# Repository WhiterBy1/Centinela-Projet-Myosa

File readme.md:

# CENTINELA — Arquitectura de Firmware y Procesamiento de Datos

**Versión:** borrador v0.1
**Base:** esquemático KiCad (ESP32-S2-WROVER + MPU6050 + BMP280 + APDS-9960 + OLED + buzzer + Adafruit Feather M0 RFM9x)

Este documento define, a nivel de código, cómo el firmware de la pulsera CENTINELA adquiere datos de cada sensor, cómo se procesan, qué valores finales produce y cómo esos valores se usan para decidir y transmitir una alerta.

---

## 1. Resumen del sistema

CENTINELA es una pulsera IoT/Edge AI que detecta inmovilidad anómala sostenida en trabajadores agrícolas aislados. El ESP32-S2 corre un clasificador TinyML sobre datos inerciales del MPU6050. Si detecta una posible caída/incapacitación, abre una ventana de confirmación de 60 s en la que el trabajador puede cancelar con un gesto (APDS-9960). Si no cancela, se transmite una alerta por LoRa a una estación base y se visualiza en una torre de control web.

### 1.1 Diagrama de flujo general

Vista de extremo a extremo: desde la muestra cruda del IMU hasta que la alerta aparece en la torre de control. Detalle de cada bloque en las secciones 4 a 7.

```mermaid
flowchart TD
    A["MPU6050: accel/gyro @ 50 Hz"] --> B["Filtro DLPF (hardware, ~20 Hz)"]
    B --> C["Ventana deslizante (64 muestras, 75% solape)"]
    C --> D["Extracción de features"]
    D --> E["Clasificador TinyML (int8)"]
    E --> F{"score >= 0.75?"}
    F -- No --> G["consecutive_immobile = 0"]
    G --> C
    F -- Si --> H["consecutive_immobile++"]
    H --> I{"consecutive_immobile >= 8 ventanas?"}
    I -- No --> C
    I -- Si --> J["EV_SUSPECTED_IMMOBILITY"]

    J --> K["STATE_SUSPECTED_IMMOBILITY\nOLED + buzzer patrón bajo"]
    K --> L["STATE_CONFIRMATION_WINDOW (60 s)"]
    L --> M{"Gesto de cancelación\n(APDS-9960)?"}
    M -- Si --> N["STATE_NORMAL\n+ log de falso positivo"]
    M -- "No (timeout 60s)" --> O["Armar centinela_packet_t"]

    P["BMP280: temperatura"] -.->|"severity_bonus"| O
    Q["APDS-9960: gesto de zona"] -.->|"zone_id"| O

    O --> R["STATE_ALERT_TRANSMITTING\n(envío por LoRa vía Feather M0)"]
    R --> S{"ACK recibido?"}
    S -- "No (timeout ACK)" --> T{"reintentos < N?"}
    T -- Si --> R
    T -- No --> U["Modo baliza persistente"]
    S -- Si --> V["STATE_ALERT_ACKED\nbuzzer confirmación + OLED"]
    V --> W["Estación base"]
    W --> X["Torre de control web\n(panel del supervisor)"]
```

---

## 2. Mapa de hardware y buses

Según el esquemático:

| Componente | Ref. | Interfaz | Notas |
|---|---|---|---|
| MPU6050 (IMU) | U1 | I2C compartido (SDAD/SCLD) | VLOGIC/VDD a 3.3V, AD0 a GND → dirección 0x68 |
| BMP280 (temp/presión) | U2 | I2C compartido (SDAD/SCLD) | Sustituye al BMP180 mencionado en la propuesta original |
| APDS-9960 (gestos/proximidad/luz) | U3 | I2C compartido (SDAD/SCLD) + línea INT dedicada | INT usado como interrupción de gesto/wake |
| OLED 0.91" | U5 | I2C compartido (SDAD/SCLD) | Solo display, sin touch |
| Buzzer | BZ1 | GPIO digital directo | Control por PWM/tono |
| Adafruit Feather M0 RFM9x (LoRa) | A1 | SPI (SCK/MOSI/MISO) + UART (RX/TX) + I2C + EN/RESET | Actúa como **co-procesador de radio**, no como módulo RFM9x desnudo |

**Nota importante sobre el bloque LoRa:** el esquemático conecta al Feather M0 casi todos sus buses (SPI, UART, I2C, EN/RESET). Esto implica una decisión de arquitectura que conviene fijar por escrito antes de programar:

- **Opción A — SPI directo:** el ESP32-S2 es maestro SPI y el Feather M0 corre un firmware "esclavo" que traduce comandos SPI a operaciones del RFM9x (RadioHead/LoRa.h). Más rápido, pero requiere firmware custom en el SAMD21 del Feather.
- **Opción B — UART tipo módem:** el Feather M0 corre un firmware con protocolo de comandos simple sobre RX/TX (similar a comandos AT), y el ESP32 solo envía/recibe tramas de texto o binarias por serial. Más simple de depurar, menor throughput.

Se recomienda **Opción B (UART)** para el prototipo por velocidad de desarrollo, dejando SPI como mejora futura si se necesita menor latencia. *(Pendiente de confirmar según lo que ya se implementó en el Feather.)*

Todos los sensores I2C comparten bus, por lo que el firmware debe direccionarlos individualmente (direcciones por defecto: MPU6050 `0x68`, BMP280 `0x76/0x77`, APDS-9960 `0x39`, OLED SSD1306-like `0x3C`).

---

## 3. Arquitectura de firmware (FreeRTOS, dual-core)

El ESP32-S2 corre FreeRTOS con tareas repartidas así:

```
Core 0 (protocol/sensor core)          Core 1 (application core)
├── Task_SensorAcquisition (50 Hz)     ├── Task_Inference (TinyML)
├── Task_EnvSample (1 Hz, BMP280)      ├── Task_StateMachine
├── Task_GestureISR (event-driven)     ├── Task_LoRaComm
└── Task_PowerMgmt                     └── Task_UI (OLED + buzzer)
```

Comunicación entre tareas vía colas (`QueueHandle_t`) y un buffer circular protegido por mutex para las muestras del IMU.

```c
// Buffer de ventana deslizante para el clasificador
#define WINDOW_SIZE   64      // muestras (a 50 Hz ≈ 1.28 s de ventana)
#define WINDOW_STRIDE 16      // solape del 75%

typedef struct {
  int16_t ax, ay, az;   // acelerómetro crudo (LSB)
  int16_t gx, gy, gz;   // giroscopio crudo (LSB)
  uint32_t t_ms;
} imu_sample_t;

static imu_sample_t imu_window[WINDOW_SIZE];
static SemaphoreHandle_t imu_mutex;
static QueueHandle_t q_inference_result;
static QueueHandle_t q_state_events;
```

---

## 4. Adquisición de datos por dispositivo

### 4.1 MPU6050 — sensor primario del clasificador

- **Datos crudos:** aceleración (ax, ay, az) y velocidad angular (gx, gy, gz), 16 bits cada eje.
- **Frecuencia:** 50 Hz vía FIFO interno del MPU6050 (reduce carga de I2C frente a polling por registro).
- **Escalas configuradas:** ±4g (acelerómetro), ±500°/s (giroscopio) — suficiente para capturar caída sin saturar en golpe.
- **Preprocesamiento:**
  1. Conversión LSB → unidades físicas (g, °/s). El MPU6050 no entrega directamente "g" ni "°/s", entrega enteros crudos de 16 bits que hay que dividir por un factor de sensibilidad. Ese factor está definido en el datasheet del fabricante (InvenSense, *MPU-6050 Register Map and Descriptions*, tabla de sensibilidad del acelerómetro/giroscopio) y depende del rango full-scale configurado:

     | Sensor | Rango configurado | Sensibilidad (datasheet) | Fórmula |
     |---|---|---|---|
     | Acelerómetro | ±4g (`ACCEL_RANGE_4G`) | 8192 LSB/g | `accel_g = raw / 8192.0` |
     | Giroscopio | ±500°/s (`GYRO_RANGE_500DPS`) | 65.5 LSB/(°/s) | `gyro_dps = raw / 65.5` |

     Si más adelante se cambia el rango en `mpu6050_init()` (ej. a ±2g u ±8g), hay que usar la sensibilidad correspondiente a ese rango — no es la misma constante para todos los rangos.
  2. Filtro pasa-bajas (DLPF interno del MPU6050, ~20 Hz) para quitar vibración de alta frecuencia.
  3. Cálculo de magnitud de aceleración: `|a| = sqrt(ax² + ay² + az²)`.
  4. Ventaneo (64 muestras, solape 75%) y extracción de features antes de pasar al modelo (sección 5).

```c
void task_sensor_acquisition(void *arg) {
  mpu6050_init(ACCEL_RANGE_4G, GYRO_RANGE_500DPS, DLPF_20HZ);
  while (1) {
    imu_sample_t s;
    mpu6050_read_fifo(&s.ax, &s.ay, &s.az, &s.gx, &s.gy, &s.gz);
    s.t_ms = millis();
    xSemaphoreTake(imu_mutex, portMAX_DELAY);
    imu_window_push(&s);
    xSemaphoreGive(imu_mutex);
    vTaskDelay(pdMS_TO_TICKS(20)); // 50 Hz
  }
}
```

### 4.2 BMP280 — variable de contexto ambiental

- **Datos crudos:** temperatura (°C) y presión (hPa, opcional).
- **Frecuencia:** 1 muestra/60 s (forced mode, bajo consumo) — no es señal de decisión, solo contexto.
- **Uso:** modula la **prioridad de la alerta** (ej. temperatura ambiente >35°C sube el nivel de severidad, porque un trabajador inmóvil bajo sol directo tiene mayor riesgo de golpe de calor mientras espera rescate).

```c
float temp_c = bmp280_read_temperature();  // forced mode
uint8_t severity_bonus = (temp_c > 35.0f) ? 1 : 0;
```

### 4.3 APDS-9960 — interacción por gestos (triple función)

- **Datos crudos:** eventos de gesto (UP/DOWN/LEFT/RIGHT), proximidad (0–255), y luz ambiental/color (opcional, no usado en MVP).
- **Modo de lectura:** **event-driven**, no polling — el pin `INT` del APDS-9960 dispara una ISR en el ESP32 solo cuando hay proximidad/gesto detectado. Esto es clave para bajo consumo.
- **Tres funciones del mismo sensor:**
  1. **Wake-up por hardware:** en deep sleep, el `INT` del APDS-9960 es la fuente de interrupción externa (`esp_sleep_enable_ext0_wakeup`) que saca al ESP32 del sueño profundo.
  2. **Declaración de zona (check-in):** el trabajador hace un gesto específico (ej. swipe derecha) al iniciar labor en una zona de la finca; el firmware mapea el gesto a un `zone_id` (1–4) que se adjunta a cada paquete LoRa, ya que no hay GPS.
  3. **Cancelación de alarma:** durante la ventana de confirmación de 60 s, un gesto (ej. swipe izquierda) cancela la alerta antes de transmitir.

```c
void IRAM_ATTR apds_isr_handler(void *arg) {
  BaseType_t hp_woken = pdFALSE;
  gesture_event_t evt = GESTURE_PENDING;
  xQueueSendFromISR(q_gesture_events, &evt, &hp_woken);
  if (hp_woken) portYIELD_FROM_ISR();
}
```

### 4.4 OLED — diagnóstico local

- **Qué muestra:** estado del sistema (`NORMAL` / `SOSPECHA` / `CONFIRMANDO (Ns restantes)` / `ALERTA ENVIADA`), nivel de batería, zona activa, indicador de enlace LoRa (última confirmación recibida).
- **Frecuencia de refresco:** 1 Hz o solo en cambio de estado (para ahorrar energía; el OLED se apaga en deep sleep).

### 4.5 Buzzer — retroalimentación audible

- **Patrones de tono escalonados según severidad:**

| Estado | Patrón |
|---|---|
| Entrando a ventana de confirmación | 1 beep corto cada 5 s |
| Últimos 10 s de la ventana | beep continuo intermitente rápido |
| Alerta transmitida (sin ACK) | tono grave sostenido |
| Alerta confirmada por estación base (ACK) | 2 beeps agudos |

```c
void buzzer_pattern(alert_severity_t sev) {
  switch (sev) {
    case SEV_LOW:    tone(BUZZER_PIN, 1000, 150); break;
    case SEV_MEDIUM:  tone(BUZZER_PIN, 2000, 300); break;
    case SEV_HIGH:   tone(BUZZER_PIN, 3000, 600); break;
  }
}
```

### 4.6 Módulo LoRa (Feather M0 RFM9x) — comunicación

- **Rol:** co-procesador de radio, ver sección 2. Recibe del ESP32 una trama ya construida y la transmite; retorna ACK/estado del enlace.
- **Topología:** estrella — la pulsera solo habla con la estación base; la estación base retransmite a la torre de control web.
- **Bidireccional:** la torre de control puede empujar mensajes hacia la pulsera (ej. "alerta reconocida por supervisor", "falso positivo confirmado por central").

---

## 5. Pipeline de procesamiento de señales

```
IMU raw (50 Hz)
   → filtro DLPF (hardware)
   → ventana deslizante (64 muestras / 75% solape)
   → extracción de features
   → clasificador TinyML (int8)
   → immobility_score (0.0–1.0)
   → lógica de umbral + duración sostenida
   → evento de estado (STATE_SUSPECTED_IMMOBILITY)
```

**Features extraídas por ventana** (antes de la red, o como capa de entrada según el diseño del modelo):

- Media y desviación estándar de `|a|` (magnitud de aceleración).
- Energía de la señal (suma de cuadrados) en cada eje.
- Cruces por cero de la derivada (proxy de actividad/temblor).
- Magnitud media del giroscopio.

**Criterio de inmovilidad sostenida** (no solo un frame): el modelo puede clasificar una ventana individual como "inmóvil", pero solo se dispara sospecha si **N ventanas consecutivas** (ej. 8 ventanas ≈ ~10 s reales considerando el solape) superan el umbral. Esto evita falsos positivos por micro-pausas normales.

```c
#define IMMOBILITY_THRESHOLD   0.75f
#define CONSECUTIVE_WINDOWS_REQ 8

static uint8_t consecutive_immobile = 0;

void task_inference(void *arg) {
  while (1) {
    float features[N_FEATURES];
    extract_features(imu_window, features);
    float score = tflite_infer(features);   // TinyML int8

    if (score >= IMMOBILITY_THRESHOLD) {
      consecutive_immobile++;
    } else {
      consecutive_immobile = 0;
    }

    if (consecutive_immobile >= CONSECUTIVE_WINDOWS_REQ) {
      state_event_t ev = EV_SUSPECTED_IMMOBILITY;
      xQueueSend(q_state_events, &ev, 0);
      consecutive_immobile = 0; // evita re-disparo mientras ya está en ventana de confirmación
    }
    vTaskDelay(pdMS_TO_TICKS(WINDOW_STRIDE * 20)); // ritmo de nuevas ventanas
  }
}
```

---

## 6. Máquina de estados

```c
typedef enum {
  STATE_NORMAL,
  STATE_SUSPECTED_IMMOBILITY,
  STATE_CONFIRMATION_WINDOW,   // 60 s, cancelable por gesto
  STATE_ALERT_TRANSMITTING,
  STATE_ALERT_ACKED,
  STATE_DEEP_SLEEP
} centinela_state_t;
```

| Transición | Disparador | Acción |
|---|---|---|
| NORMAL → SUSPECTED_IMMOBILITY | `EV_SUSPECTED_IMMOBILITY` del clasificador | Enciende OLED, inicia buzzer patrón bajo |
| SUSPECTED_IMMOBILITY → CONFIRMATION_WINDOW | inmediato | Timer de 60 s, escucha `q_gesture_events` |
| CONFIRMATION_WINDOW → NORMAL | gesto de cancelación detectado | Log local del falso positivo (para reentrenar el modelo después) |
| CONFIRMATION_WINDOW → ALERT_TRANSMITTING | timeout de 60 s sin cancelación | Arma paquete LoRa (sección 7) y transmite |
| ALERT_TRANSMITTING → ALERT_ACKED | ACK recibido de estación base | Buzzer confirmación, OLED "Ayuda en camino" |
| ALERT_TRANSMITTING → ALERT_TRANSMITTING (reintento) | timeout de ACK (ej. 5 s) | Reintenta hasta N veces, luego pasa a modo persistente de baliza |
| cualquier estado activo → DEEP_SLEEP | inactividad prolongada en NORMAL | Apaga periféricos, deja solo INT del APDS-9960 como wake source |

### 6.1 Diagrama de estados (Mermaid)

```mermaid
stateDiagram-v2
    [*] --> NORMAL
    NORMAL --> DEEP_SLEEP: inactividad prolongada
    DEEP_SLEEP --> NORMAL: wake (INT APDS-9960)
    NORMAL --> SUSPECTED_IMMOBILITY: EV_SUSPECTED_IMMOBILITY (clasificador)
    SUSPECTED_IMMOBILITY --> CONFIRMATION_WINDOW: inmediato
    CONFIRMATION_WINDOW --> NORMAL: gesto de cancelación
    CONFIRMATION_WINDOW --> ALERT_TRANSMITTING: timeout 60s sin cancelación
    ALERT_TRANSMITTING --> ALERT_TRANSMITTING: timeout ACK, reintento < N
    ALERT_TRANSMITTING --> ALERT_ACKED: ACK recibido
    ALERT_TRANSMITTING --> [*]: reintentos agotados (modo baliza)
    ALERT_ACKED --> NORMAL: incidente cerrado
```

---

## 7. Protocolo LoRa — estructura de paquete y valores finales

Este es el **valor final** que produce todo el pipeline: un paquete compacto que la estación base reenvía a la torre de control web.

```c
typedef struct __attribute__((packed)) {
  uint8_t  device_id;        // ID único de la pulsera
  uint8_t  packet_type;      // 0=heartbeat, 1=alerta, 2=cancelación_log, 3=ack_confirm
  uint8_t  alert_severity;   // 0=info,1=bajo,2=medio,3=alto (modulado por temperatura)
  float    immobility_score; // último score del clasificador (0.0-1.0), trazabilidad
  float    temperature_c;    // contexto ambiental (BMP280)
  uint8_t  zone_id;          // zona declarada por gesto (1-4), sustituto de GPS
  uint16_t battery_mv;       // estado de batería 18650
  uint32_t timestamp_ms;     // uptime del dispositivo (o RTC si se agrega)
  uint8_t  checksum;         // XOR o CRC8 de los campos anteriores
} centinela_packet_t;        // 20 bytes — cabe cómodo en un payload LoRa
```

- **Heartbeat:** cada N minutos en estado NORMAL, para que la torre de control sepa que la pulsera sigue viva (packet_type=0). Frecuencia a definir según presupuesto de energía (ej. cada 10 min).
- **Alerta:** packet_type=1, con severidad calculada como `base_severity(immobility_score) + severity_bonus(temp_c)`.
- **Log de cancelación:** packet_type=2, opcional/diferido — puede acumularse localmente y enviarse en el próximo heartbeat en vez de gastar batería en una transmisión inmediata, ya que no es una emergencia.

**En la torre de control (lado servidor/web):** cada paquete recibido se decodifica y se persiste con al menos estos campos: `device_id`, `zone_id`, `alert_severity`, `immobility_score`, `temperature_c`, `battery_mv`, `received_at` (timestamp del servidor, no del dispositivo, para evitar depender de reloj no sincronizado del ESP32). Este es el registro que finalmente ve el supervisor en el panel web y sobre el cual se dispara la notificación humana.

---

## 8. Gestión de energía

- **Deep sleep** en estado NORMAL tras un periodo de inactividad sostenida detectada por el propio IMU (baja varianza) — reduce muestreo o entra a sleep con wake por `INT` del APDS-9960 (hardware interrupt, sin polling).
- El módulo LoRa (Feather M0) puede tener su propio sleep coordinado por el pin `EN/RESET` visible en el esquemático, apagándose entre heartbeats.
- Batería 18650 con regulación lineal (AMS1117) — implica que la lectura de `battery_mv` debe hacerse antes del regulador o vía un divisor resistivo dedicado a un ADC del ESP32 (pendiente de confirmar si el esquemático ya contempla ese divisor; no se ve en la vista actual).

---

## 9. Pendientes a definir antes de codificar

1. Confirmar protocolo real ESP32 ↔ Feather M0 (SPI directo vs UART, sección 2).
2. Confirmar si existe divisor resistivo para medir voltaje de batería por ADC.
3. Definir arquitectura exacta de la red (dense vs 1D-CNN, nº de capas) y ejecutar el entrenamiento — ver sección 10 para el plan concreto de datos y pipeline.
4. Definir número de reintentos y timeout de ACK en el protocolo LoRa.
5. Definir si el log de cancelaciones (falsos positivos) se usa para reentrenamiento offline del modelo.

---

## 10. Modelo TinyML — qué es, cómo se entrena y dónde conseguir datos

Esta sección estaba pendiente. Responde tres preguntas: **qué** clasifica el modelo, **con qué datos** se entrena, y **dónde/cómo** se entrena y se lleva al ESP32-S2.

### 10.1 Dónde vive el entrenamiento (importante entenderlo primero)

El ESP32 **nunca entrena**. El entrenamiento se hace una sola vez, offline, en una laptop/PC con Python. El resultado es un archivo `.tflite` cuantizado a int8, que se convierte a un arreglo de bytes en C (`model_data[]`) y se compila dentro del firmware. En tiempo real, el ESP32 solo corre `tflite_infer()` (inferencia pura, sin aprendizaje) sobre ese modelo ya congelado. Si más adelante quieren reentrenar con datos nuevos (ej. los falsos positivos logueados, ver sección 6), se repite el ciclo offline y se reflashea el dispositivo — no hay aprendizaje "en vivo" en la pulsera.

### 10.2 Qué debería clasificar el modelo, realmente

Vale la pena separar dos cosas que hoy están mezcladas conceptualmente:

- La **inmovilidad sostenida** (bajo movimiento durante muchas ventanas seguidas) ya la resuelve la lógica determinística de la sección 5 (`consecutive_immobile >= 8`) — **eso no necesita red neuronal**, es un umbral sobre features estadísticos y funciona sin entrenar nada.
- Donde una red sí aporta valor real es detectando el **patrón característico de una caída/impacto** (pico brusco de aceleración seguido de calma), que es más difícil de capturar con un umbral simple y es justamente lo que existe como dataset público entrenable.

Recomendación: entrenar un **clasificador binario por ventana** `CAÍDA` vs `ACTIVIDAD_NORMAL` (o multiclase si quieren distinguir caminar/trabajar/sentado/caída). Ese `immobility_score` de la sección 5 pasa a ser, en la práctica, la probabilidad de la clase `CAÍDA` que entrega el modelo. La lógica de ventanas consecutivas sigue funcionando igual como filtro anti-falsos-positivos después de la predicción.

### 10.3 De dónde salen los datos de entrenamiento

No existe un dataset público hecho a la medida de "pulsera ESP32 + MPU6050 en trabajador agrícola", pero sí hay datasets públicos de detección de caídas con sensor **en la muñeca** que sirven de punto de partida:

| Dataset | Ubicación del sensor | Tamaño | Frecuencia | Notas |
|---|---|---|---|---|
| [FallAllD](https://www.researchgate.net/publication/378760322_Wrist-Based_Fall_Detection_Towards_Generalization_across_Datasets) | cuello, cintura **y muñeca** | 15 sujetos, 6605 instancias (1722 caídas, 4883 AVD) | alta (IMU dedicado) | El más citado para fall detection multi-posición, incluye muñeca por separado |
| [HR_IMU fall dataset](https://github.com/nhoyh/HR_IMU_falldetection_dataset) | muñeca (mano izquierda) | 21 sujetos, 19 escenarios (6 caídas, 9 AVD, 4 casi-caídas) | **50 Hz — igual que su firmware** | Coincide con la frecuencia ya configurada en `task_sensor_acquisition()` |
| [Geriatric wrist-worn dataset](https://www.ncbi.nlm.nih.gov/pmc/articles/PMC10709028/) | muñeca, dispositivo custom | 41 sujetos, 16 AVD + 8 caídas | IMU + frecuencia cardíaca | Población de adultos mayores, útil si buscan robustez ante marcha lenta |
| [UP-Fall Detection](https://www.mdpi.com/1424-8220/24/5/1679) | muñeca (simula smartwatch) | 70 secuencias (30 caídas, 40 AVD) | — | Multisensor, incluye cámaras además de IMU |

`HR_IMU` es probablemente el mejor punto de partida porque ya está muestreado a 50 Hz, la misma frecuencia que configuraron en el MPU6050.

### 10.4 Adaptar los datos públicos a su hardware

1. Verificar orientación de ejes del dataset vs. cómo queda montado el MPU6050 en la pulsera física (si no coincide, hay que rotar los ejes en el preprocesamiento, no reentrenar el sensor).
2. Re-muestrear a 50 Hz si el dataset elegido usa otra frecuencia.
3. Cortar en ventanas de 64 muestras con 75% de solape — exactamente el mismo esquema de `WINDOW_SIZE`/`WINDOW_STRIDE` de la sección 3, para que el modelo entrenado "vea" datos con la misma forma que verá en producción.
4. Calcular los mismos features de la sección 5 (media/desv. de `|a|`, energía por eje, cruces por cero, magnitud media del giroscopio) si van con una red densa pequeña — o usar la ventana cruda si optan por una 1D-CNN.

### 10.5 Entrenamiento — dos caminos

**Opción A — Edge Impulse (recomendada para empezar rápido).** Plataforma web con soporte oficial para ESP32: suben el CSV de datos (público + el suyo propio), extraen features automáticamente, entrenan la red desde el navegador, cuantizan a int8 y exportan una librería C++ lista para compilar — sin tener que escribir a mano el pipeline de TensorFlow ni la conversión a TFLite Micro. Es el camino más corto de "tengo datos" a "tengo firmware".

**Opción B — TensorFlow/Keras manual + TensorFlow Lite Micro.** Más control, más trabajo: entrenar en Python con Keras (red densa pequeña de 2-3 capas sobre los features, o una 1D-CNN sobre la ventana cruda si la densa no alcanza precisión suficiente), convertir con `TFLiteConverter` usando un dataset representativo para cuantización int8, generar el arreglo C con `xxd -i model.tflite > model_data.h`, e integrar con la librería `esp-tflite-micro` en el proyecto ESP-IDF/Arduino.

Para un modelo de este tamaño (pocos features de entrada, 2-3 capas), el `.tflite` cuantizado debería pesar unos pocos KB — sin problema para la flash/RAM del ESP32-S2-WROVER.

### 10.6 El paso que no pueden saltarse: datos propios con el hardware real

Los datasets públicos están grabados con sensores distintos, en muñecas distintas, en gente haciendo actividades distintas a labores de campo. Es dominio parecido, no idéntico — un modelo entrenado *solo* con datos públicos casi seguro no generalizará bien a la demo en vivo. El plan realista:

1. Usar el dataset público (`HR_IMU` u otro) para validar que el pipeline de entrenamiento + cuantización + despliegue funciona de punta a punta.
2. Grabar un dataset propio, pequeño, con la pulsera real: ustedes dos (y si pueden, más voluntarios) haciendo actividades tipo labor de campo (caminar, agacharse, cargar objetos) y caídas simuladas controladas (sobre colchoneta), etiquetando cada sesión.
3. Reentrenar o hacer fine-tuning del modelo con esos datos propios antes de la demostración final — es lo que va a hacer que el clasificador funcione bien con *su* hardware y *su* forma de usarlo.

### 10.7 Validación

Antes de dar el modelo por bueno: separar un conjunto de prueba (datos que el modelo no vio en entrenamiento), revisar matriz de confusión (interesa sobre todo la tasa de falsos negativos — una caída real no detectada es el peor caso), y medir en el propio ESP32 el tiempo de inferencia y el uso de RAM del "tensor arena" de TFLite Micro para confirmar que corre cómodo a la par de las demás tareas de FreeRTOS.

---

*Este documento es la base para dividir el trabajo en módulos de firmware (adquisición, inferencia, máquina de estados, comunicación, energía) y puede versionarse a medida que se confirmen los pendientes de la sección 9.*

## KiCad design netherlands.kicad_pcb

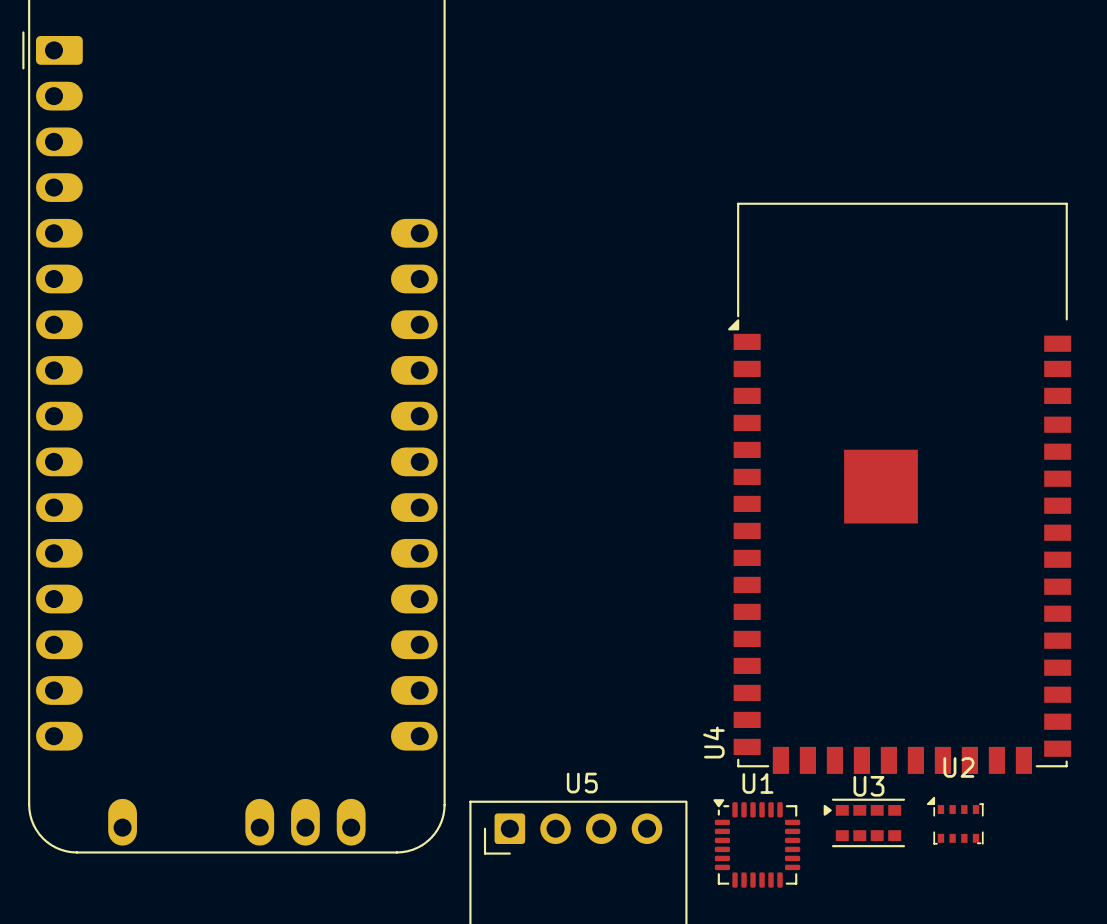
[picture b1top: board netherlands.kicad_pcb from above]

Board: 2 copper layers, 6 parts (0 on the bottom side), 10 nets, no tracks yet.

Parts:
A1: Adafruit_Feather_M0_RFM9x_LoRa_Radio; Adafruit_Feather_M0_RFM
U1: MPU-6050; InvenSense_QFN-24_4x4mm_P0.5mm
U2: BMP280; Bosch_LGA-8_2x2.5mm_P0.65mm_ClockwisePinNumbering
U3: APDS-9960; Avago_APDS-9960
U4: ESP32-S2-WROVER
U5: ER_OLEDM0.91_1x-I2C

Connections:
/SCL: U1.23 (SCL), U2.4 (SCK), U3.7 (SCL), U4.21 (IO18), U5.3 (SCL)
/SDA: U1.24 (SDA), U2.5 (SDO), U3.1 (SDA), U4.24 (IO21), U5.4 (SDA)
unnamed: A1.2 (3V3), U1.13 (VDD), U2.8 (VDD), U4.2 (3V3), U5.2 (VCC)
unnamed: A1.21 (D9), U4.17 (IO14)
unnamed: A1.22 (D10), U4.28 (IO34)
unnamed: A1.4 (GND), U1.18 (GND), U2.1 (GND), U3.6 (GND), U4.1 (GND), U4.26 (GND), U4.42 (GND), U4.43 (GND), U5.1 (GND)
unnamed: A1.13 (MISO/D22), U4.31 (IO37)
unnamed: A1.12 (MOSI/D23), U4.29 (IO35)
unnamed: A1.11 (SCK/D24), U4.30 (IO36)
unnamed: A1.1 (~RESET), U4.15 (IO12)
